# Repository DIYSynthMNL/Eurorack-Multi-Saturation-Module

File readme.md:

# Synth Distortion / Saturation Module Design

## Revision Summary

- Schematic Revision 0.5 - an easier to read schematic - please note that there are some errors in this. The Eurorack power connector pins are backwards. Use this as a reference for the circuit design.
- Schematic Revision 0.6 - multiboard layout (LATEST - working on circuit revisions)
- PCB Revision 0.1 - revising in progress (working on rev 0.2)

## Some background.

I’m designing a distortion/saturation modular synth module using different methods of distorting audio signals.

This module is a combination of transformer, opto, and clipping distortion/saturation.

## Source of inspiration

Local archived copies of the borrowed-source schematics live in [`references/`](references/) so this repo stays useful if the upstream links die. Originals from [diyrecordingequipment.com](https://www.diyrecordingequipment.com/pages/the-colour-format).

- **CTX Cinemag Transformer Colour mkII** — [local copy](references/DIYRE-CTX-Cinemag-mkII-schematic.pdf) · [upstream](https://cdn.shopify.com/s/files/1/0698/2265/files/CTX_mkII_Schematic.pdf?375)
- **Colourphone (v1.3)** — [local copy](references/DIYRE-Colourphone-schematic-v1.3.pdf) · [upstream](https://cdn.shopify.com/s/files/1/0698/2265/files/XQP_Colourphone_Schematic_1.3.pdf?8973696934571457842)
- **Colourupter (v1.7)** — [local copy](references/DIYRE-Colourupter-schematic-v1.7.pdf) · [upstream](https://cdn.shopify.com/s/files/1/0698/2265/files/XQP_Colourupter_Schematic_1.7.pdf?13355729951948932441)

### DIYRe’s Colour Modules

I got some ideas from DIYRe's Colour modules. DIYRe is a company that produces DIY kits for professional audio recording equipment. Some of their product offerings include recording studio rackmount effects.

[The Colour Format](https://www.diyrecordingequipment.com/pages/the-colour-format)

| Colour Module | What does it do? | What ideas did you get? | Link to page | Schematic |
| --- | --- | --- | --- | --- |
| CTX Transformer Colour | A transformer saturation module with a discrete opamp and a Cinemag audio transformer which has a 1:1 turns ratio. | Non-inverting amp to drive the transformer past what it can handle. Resistor before the transformer that isolates the opamp from the transformer. | https://www.diyrecordingequipment.com/products/ctx-cinemag-transformer-colour-mkii | https://cdn.shopify.com/s/files/1/0698/2265/files/CTX_mkII_Schematic.pdf?375 |
| Colourphone | A telephone sound emulator. It uses a bandpass filter and a 1:1 turn ratio audio transformer. | I have a similar transformer which is a 600:600 ohm transformer. Resistor before the transformer that isolates it from the opamp. | https://www.diyrecordingequipment.com/products/colourphone-telephone-distortion-colour | https://cdn.shopify.com/s/files/1/0698/2265/files/XQP_Colourphone_Schematic_1.3.pdf?8973696934571457842 |
| Colourupter | An opto distortion module that is vactrol based. | Using a vactrol and the circuit around it. IC1c and IC1d only. | https://www.diyrecordingequipment.com/products/colourupter | https://cdn.shopify.com/s/files/1/0698/2265/files/XQP_Colourupter_Schematic_1.7.pdf?13355729951948932441 |

### Other sources

- Vactrol wet/dry mix from music thing modular’s spring reverb module
    - [https://www.musicthing.co.uk/Spring-Reverb/](https://www.musicthing.co.uk/Spring-Reverb/)
- Eliot Sound Products [https://sound-au.com](https://sound-au.com/) - is a website full of audio articles that I’ve learned from. Go search for these articles, they’re great!
    - Designing With Op Amps
    - Audio Transformers
    - Soft Clipping

# Circuit Design

- I will update this section soon.

### Stages

1. Input gain stage (buffer only, see design note below)

    We must take into account the headroom of the op amp. The NE5532 can only output 2 volts less than the supply voltage. So for example, your supply voltage would be +/- 12V, your max output would be 10V based on the image below.

    A buffer would suffice as the input stage. It would be nice to give the transformer more voltage but we wouldn’t be able to amplify the 10Vpp input to 12Vpp unless we use a +/- 15V supply. 
    
    I chose to use an NE5532 Op Amp because I believe it can drive outputs higher than TL07x.
    
2. Transformer Saturation
    
    The transformer distortion works by oversaturating the transformer’s core past what it can handle. The transformer I used would normally be used in line audio signals. A 600:600 ohm transformer. We’re using Eurorack voltage which is around 10vpp so that would oversaturate the transformer.

3. Vactrol Opto Electronic Saturation
    
    The transformer’s output was low, I needed to add a non-inverting op amp with gain to bring the levels back to 10vpp for this stage.
    
    I got this circuit from DIYRe’s Colourupter colour module which uses a Vactrol to clip the signal.

4. Soft Clipping Diode Saturation
    
    I chose to place these diodes after the wet amplifier. It would be softer if I placed it before the U4A. I chained LEDs to the 1N4148s to get a softer clipping effect. LEDs alone would make saw waves looking like square waves.

5. Voltage controlled Vactrol Wet/Dry mix
    
    I used my handmade Vactrol. I made it using a 5mm diffused red LED and a 5mm LDR enclosed with black heat shrink tubing. I crimped the ends so no light would leak in. 47k works for R17 with my Vactrol.

## Schematic Revisions:

- Revision 0.2
    - TODO
        - [x]  Replace R5 with trimmer
        - [x]  Test wet/dry mix on breadboard
        - [x]  Input buffer biasing resistor
    - Notes
        - The transformer saturation is very subtle on a mono synth
- Revision 0.3
    - TODO
    - [x]  Add gain trimmer to dry signal at U2B
    - [x]  Scrap the single saturation and add diode clipping and the Colourupter, the transformer alone is too subtle
    - [x]  Test output gain stage
- Revision 0.4
    - [x]  Scrap output auto gain
    - [x]  add opto saturation
    - [x]  add soft clipping diodes
- Revision 0.5
    - [x]  Multiboard layout
- Revision 0.6
    - [ ]  Fix amplitude difference on opto sat stage output.

# PCB Design

Dec 27, 2023 - Almost satisfied  with the board design, rev0.1

Rev 0.1 in black

## PCB revisions:

- Todo for Revision 0.1
    - [x]  Ground plane vias
    - [x]  Front panel ground plane
    - [x]  Double check hole sizes
        - [x]  Trimmer
    - [x]  Double check via sizes
    - [x]  Round tracks
- Todo for Revision 0.2
    - Front panel
        - [x]  Add keep out zone for led window zone fills for FCU and BCU - I had to Dremel it out for the revision 0.1 front panel board
        - [x]  Enlarge switch holes for Dailywell switches
        - [x]  Enlarge trimmer holes
        - [x]  Change tilt knob silkscreen to “mix”
        - [ ]  Fix amplitude difference on opto sat output. The opto stage attenuates the signal from the transformer too much
- Revision 0.1 Board test notes
    - Voltage tests
        - Power rails after reverse protection diode I used a 1N4007 diode
            - V+ reads about 10V
            - V- reads about 11V
            - I might need to change the reverse protection diodes to Schottkys
    - Music thing modular’s cv wet dry circuit has an optimal input of 0-5V control voltages. If 10Vpp was used, the middle of the cv level pot is zero. Fully clockwise, the cv would be in phase. Fully counter clockwise, the cv is inverted. This is simulated in falstad, the file is included in the falstad folder.
    - Gain trim is finicky. Turning on the Opto would attenuate the signal. Maybe this is caused by the variety of the vactrol, I think not all vactrols are equal. Opto gain/amplitude trim might be required. It might be a simple resistor value change within the circuit.
    - LEDs are not as bright as I want them.

## Circuit walkthrough

Three saturation stages in series, each individually bypassable from the front panel, then a CV-controlled wet/dry mix:

```
Audio In ─► U1A buffer ─┬─► [Dry path → wet/dry mixer U4B]
                        │
                        └─► SW1 (Xformer bypass) ─► [TL016 transformer, 680Ω matching, HPF 15Hz]
                                                  ─► U1B buffer ─► transformer-saturated signal
                                                                     │
                                                                     ▼
                                                  SW2 (Opto bypass) ─► U2A buffer ─► C2 (1µF) ─► U2B inverting amp (gain −68)
                                                                                                    ├─► drives U3 vactrol LED (R10 limits)
                                                                                                    └─► AC-coupled out as "Wet"
                                                                                                                                ▼
                                              U4A amp ────────► clipping LEDs + 1N4148 (SW1 on Board B bypasses)
   Dry signal ──► U4B amp ───────────────────┘                                                              │
                                                                                                            ▼
                                                                                  U6 vactrol (CV wet/dry mixer, driven by Mix CV via U5A/U5B)
                                                                                                            ▼
                                                                                                       Mix Audio Out
```

### Three saturation flavors, switchable

**1. Transformer saturation (TL016-R, 600:600Ω).** 680Ω resistors match the transformer's characteristic impedance. Driving the primary hard pushes the magnetic core into non-linearity — classic warm "tape-like" harmonic content (mostly odd harmonics). The 15Hz HPF (C1 + R7) on the secondary removes any DC bias.

**2. Opto-electronic saturation (vactrol, U3).** U2B is a high-gain inverting amp (R8/R6 = 680/10 = **−68× gain**) driving the vactrol's LED. As the signal gets louder, the LED brightens, the LDR resistance drops, more signal shunts to ground — soft compression / saturation. Fast attack/release due to the vactrol's photo response.

**3. Diode soft clipping (Board B).** LEDs (D1, D2) in series with 1N4148s (D3, D4) — asymmetric soft clipping with the LEDs adding ~2V of softness before the 4148s contribute hard clip. Pleasant warmth without harsh square-wave look. SW1 on Board B bypasses.

### Wet/Dry mix (CV-controlled)

Borrowed from Music Thing Modular's Spring reverb topology. Second vactrol (U6) acts as a CV-controlled variable resistor in the mix path. Mix CV input → U5A → U5B → vactrol LED. The Mix Trim pot (RV4, 50K) shifts the CV center point by ±12V so the vactrol's response curve aligns with your CV source (the Music Thing original optimizes for 0–5V CV; this tuning lets it handle ±5V or other ranges).

### Calibration

Three trim pots accessible from the front panel:

**RV2 — Wet gain trim.** Sets U4A's amplification of the wet (saturated) signal. Goal: match the wet signal's amplitude to the dry signal so the mix knob crossfades cleanly.

**RV3 — Dry gain trim.** Sets U4B's amplification of the dry signal. Adjust together with RV2 until at the mix midpoint, the output amplitude doesn't jump as you switch saturation stages on/off.

**RV4 — Mix trim.** Shifts the Mix CV bias up or down ±12V. Adjust until the panel mix pot's full clockwise position gives 100% wet and full counter-clockwise gives 100% dry, with your CV source connected. With no CV connected (or 0V), midpoint should give 50/50.

Procedure:
1. Patch a steady audio signal (e.g., a sawtooth from a VCO) into Audio In.
2. Set all bypass switches to "off" (no saturation) — only the dry path is active.
3. Patch a scope on Mix Audio Out. Note the amplitude.
4. Switch in transformer saturation (SW1). Adjust RV2 (wet gain) so the amplitude is similar to dry.
5. Switch in opto saturation (SW2). If the amplitude drops dramatically here, see [issue #1](https://github.com/DIYSynthMNL/Eurorack-Multi-Saturation-Module/issues) for the known opto-sat fix.
6. With a 0–5V LFO into Mix CV, adjust RV4 (mix trim) so panel mix pot fully clockwise = wet, fully counter-clockwise = dry.

## Build status

What's ready for builders today, and what's still on the TODO list:

**Production assets** (what you need to actually fabricate and assemble a final unit)

- [x] Schematic — Rev 0.6 ([Single saturation module - Multiboard Schematic - rev0.6.pdf](Schematic%20PDFs/Single%20saturation%20module%20-%20Multiboard%20Schematic%20-%20rev0.6.pdf))
- [x] PCB layout — rev 0.1 separated for fab in `kicad/Separate boards/rev 0.1/`; rev 0.2 fixes pending (see PCB revisions in readme)
- [ ] Gerber files for fabrication — none yet
- [x] BOM — [ibom.html](BOMs/ibom.html)
- [x] Final front panel (SVG/PDF for fab) — [MultiSaturation_FPANEL_FOR_KICAD_IMPORT.svg](Front%20panel%20graphics/MultiSaturation_FPANEL_FOR_KICAD_IMPORT.svg)
- [x] License — [LICENSE](LICENSE)

**Prototype assets** (for breadboard / perfboard / 3D-printed-panel builds before final PCB)

- [ ] 3D-printed prototype panel STL — none yet

**Documentation**

- [x] Photos of the assembled module — see [photos/](photos/)
- [ ] Demo video — none yet
- [ ] Build / assembly instructions — none yet
- [ ] Calibration / tuning notes — none yet

Want to help fill a gap (build photos, gerbers, an assembly guide)? Open an issue or PR.

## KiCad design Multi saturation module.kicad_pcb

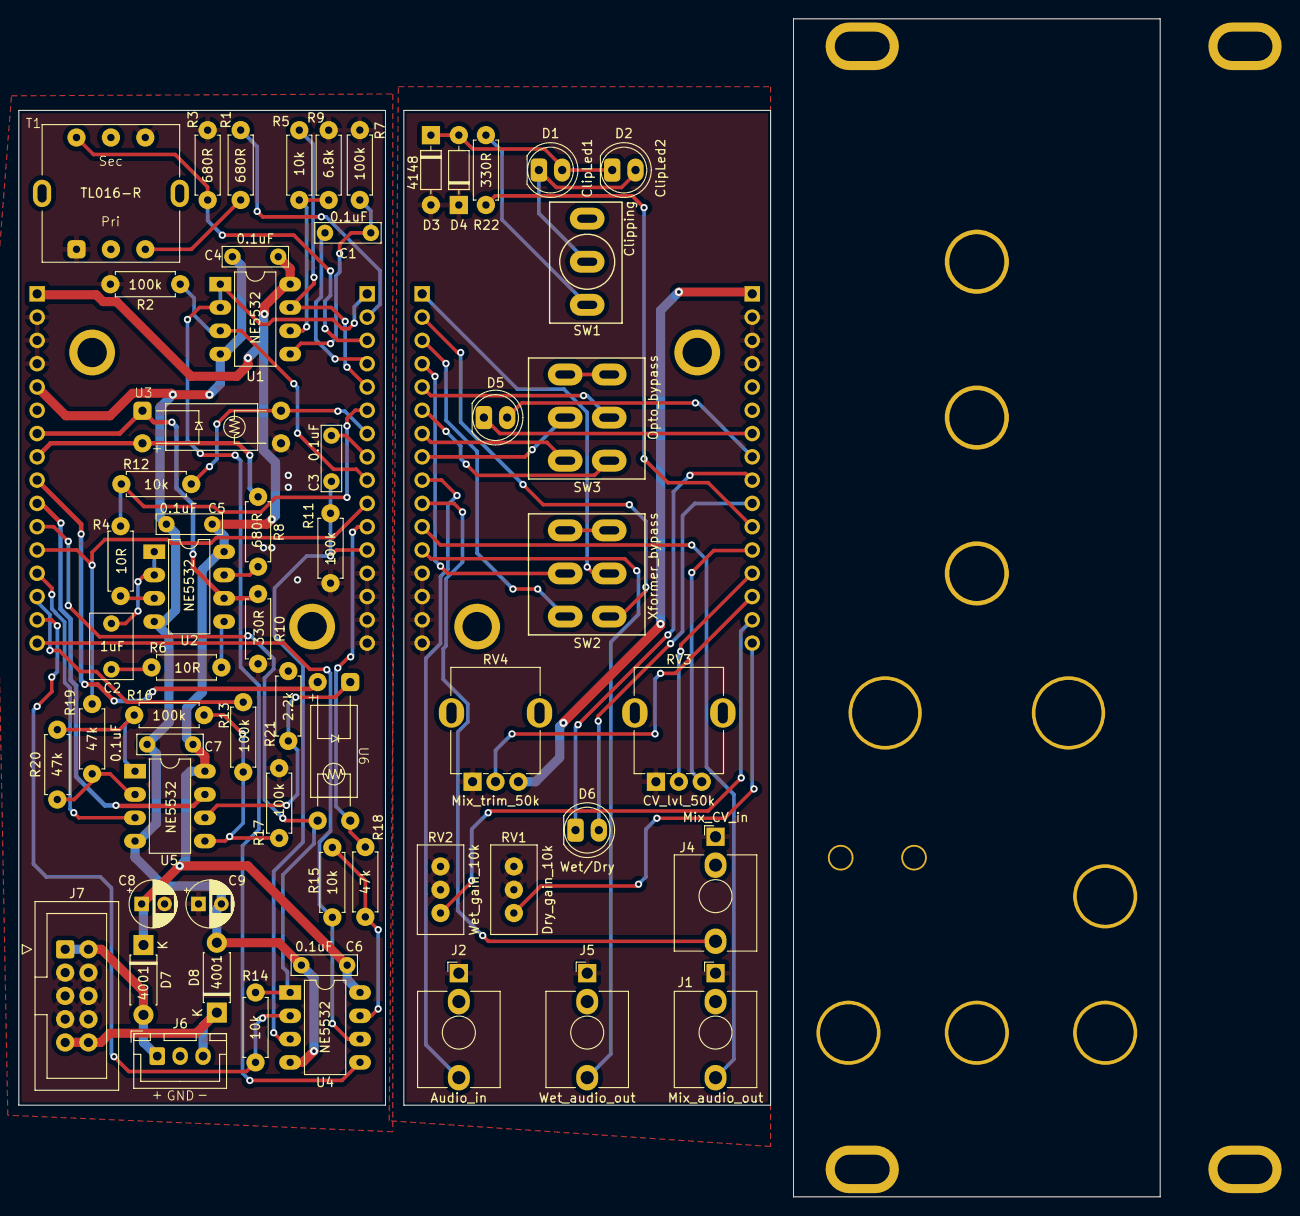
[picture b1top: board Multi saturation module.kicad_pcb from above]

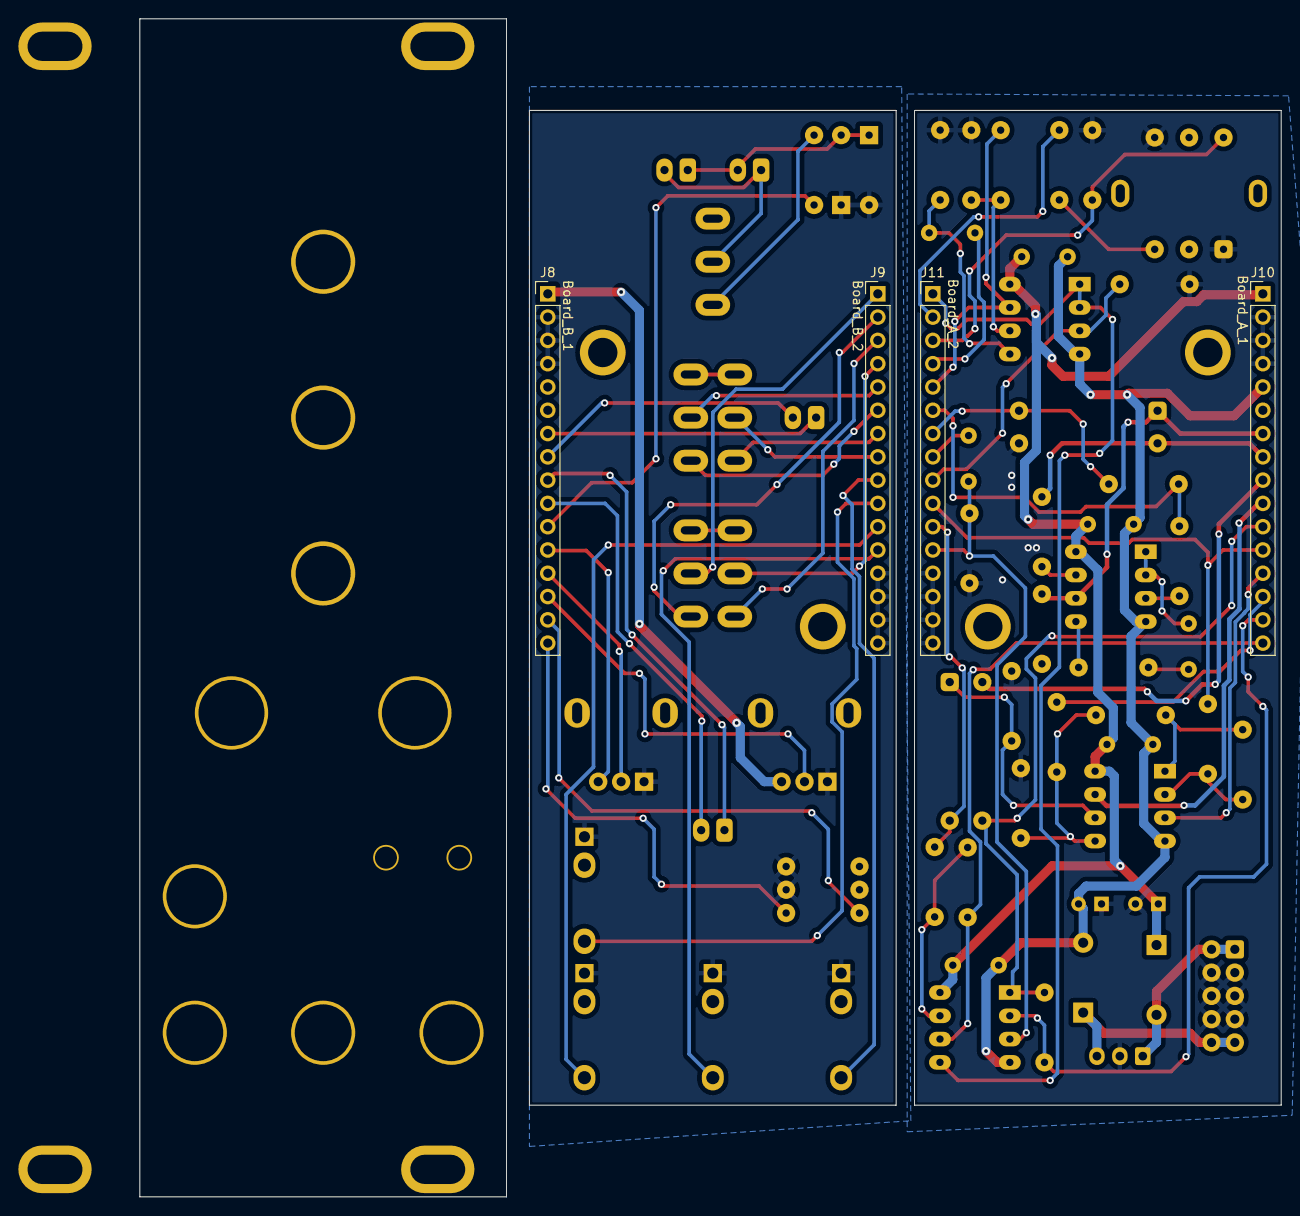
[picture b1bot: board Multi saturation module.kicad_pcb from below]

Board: 2 copper layers, 124.5 x 128.5 mm, 63 parts (4 on the bottom side), 68 nets.

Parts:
C1, C3, C4, C5, C6, C7: 0.1uF; C_Rect_L7.0mm_W2.0mm_P5.00mm_BigPads
C2: 1uF; C_Rect_L7.0mm_W4.5mm_P5.00mm_BigPads
C8, C9: 22uF; CP_Radial_D5.0mm_P2.50mm
D1: ClipLed1; LED_D5.0mm_BigPads
D2: ClipLed2; LED_D5.0mm_BigPads
D3, D4: 4148; D_4148_BigPads
D5: Opto_sat; LED_D5.0mm_BigPads
D6: Wet/Dry; LED_D5.0mm_BigPads
D7, D8: 4001; D_DO-41_SOD81_P7.62mm_Horizontal_BigPads
J1: Mix_audio_out; AudioJack_3.5mm_long_pads
J2: Audio_in; AudioJack_3.5mm_long_pads
J4: Mix_CV_in; AudioJack_3.5mm_long_pads
J5: Wet_audio_out; AudioJack_3.5mm_long_pads
J6: EuroPower_JST_3P; Eurorack_power_jst_3P
J7: EURO_PWR_2x5; IDC-Header_2x05_P2.54mm_Vertical_BigPads
J8: Board_B_1; PinHeader_1x16_P2.54mm_Vertical
J9: Board_B_2; PinHeader_1x16_P2.54mm_Vertical
J10: Board_A_1; PinHeader_1x16_P2.54mm_Vertical
J11: Board_A_2; PinHeader_1x16_P2.54mm_Vertical
R1, R3, R8: 680R; R_quarter_watt_L6.3mm_D2.5mm_P7.62mm
R2, R7, R11, R13, R16, R17: 100k; R_quarter_watt_L6.3mm_D2.5mm_P7.62mm
R4, R6: 10R; R_quarter_watt_L6.3mm_D2.5mm_P7.62mm
R5, R12, R14, R15: 10k; R_quarter_watt_L6.3mm_D2.5mm_P7.62mm
R9: 6.8k; R_quarter_watt_L6.3mm_D2.5mm_P7.62mm
R10, R22: 330R; R_quarter_watt_L6.3mm_D2.5mm_P7.62mm
R18, R19, R20: 47k; R_quarter_watt_L6.3mm_D2.5mm_P7.62mm
R21: 2.2k; R_quarter_watt_L6.3mm_D2.5mm_P7.62mm
RV1: Dry_gain_10k; Potentiometer_Bourns_3296W_Vertical_BigPads
RV2: Wet_gain_10k; Potentiometer_Bourns_3296W_Vertical_BigPads
RV3: CV_lvl_50k; Potentiometer_RV09_BigPads
RV4: Mix_trim_50k; Potentiometer_RV09_BigPads
SW1: Clipping; ToggleSwitch_MTS-102_SPDT
SW2: Xformer_bypass; ToggleSwitch_MTS-202_DPDT
SW3: Opto_bypass; ToggleSwitch_MTS-202_DPDT
T1: TL016-R; Audio_transformer_TL016-R
U1, U2, U4, U5: NE5532; DIP-8_W7.62mm_LongPads
U3, U6: VTL5C; Handmade_vactrol_5mm

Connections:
+12V: C4.1, C5.1, C6.1, C7.1, C8.1, D7.1 (K), J10.1, U1.8 (V+), U2.8 (V+), U4.8 (V+), U5.8 (V+)
+12VA: J8.1, RV4.3
-12V: C4.2, C5.2, C6.2, C7.2, C9.2, D8.2 (A), J10.5, U1.4 (V-), U2.4 (V-), U4.4 (V-), U5.4 (V-)
/Board_A/+12V_IN: D7.2 (A), J6.1 (+12v), J7.1 (+12V), J7.2 (+12V)
/Board_A/-12V_IN: D8.1 (K), J6.3 (-12v), J7.9 (-12V), J7.10 (-12V)
Audio_in: J11.9, R2.1, U1.3 (+)
Audio_in_B: J2.T, J9.9
Clipping_diodes: J10.11, R14.1, U4.1, U6.4
Clipping_diodes_B: J8.11, R22.2
D1_+: J10.8, R8.1, U3.2 (+)
D1_+_B: D5.2 (A), J8.8
D1_-: J10.7, R10.1, U2.6 (-), U3.1 (-)
D1_-_B: D5.1 (K), J8.7
D4_+: J10.10, U5.7
D4_+_B: D6.2 (A), J8.10
D4_-: J10.9, U6.2 (+)
D4_-_B: D6.1 (K), J8.9
Dry: J11.1, U1.1, U1.2 (-), U4.5 (+)
GND: C8.2, C9.1, J6.2 (GND), J7.3 (GND), J7.4 (GND), J7.5 (GND), J7.6 (GND), J7.7 (GND), J7.8 (GND), J10.2, J10.3, J10.4, J11.13, J11.14, J11.15, J11.16, R2.2, R3.1, R7.2, R9.2, R10.2, R11.2, R17.2, R21.2, T1.1, T1.4, U3.4
GND1: D3.2 (A), D4.1 (K), J1.S, J2.S, J4.S, J5.S, J8.2, J8.3, J8.4, J9.13, J9.14, J9.15, J9.16, RV1.1, RV1.2, RV2.1, RV2.2, RV3.1, RV4.1
Mix_CV_in: J10.12, J11.10, R19.1
Mix_CV_in_B: J4.T, J9.10
Mix_audio_out: J11.11, R18.1, U6.3
Mix_audio_out_B: J1.T, J9.11
unnamed: C2.2, R6.1
unnamed: D1.2 (A), D2.1 (K), D3.1 (K), D4.2 (A)
unnamed: D1.1 (K), D2.2 (A), SW1.2 (B)
unnamed: R1.2, T1.3
unnamed: R8.2, U2.7
unnamed: R15.1, R18.2, U4.7
unnamed: R16.2, R20.2, U5.1
unnamed: R22.1, SW1.1 (A)
unnamed: SW2.3 (C), SW2.6 (C)
unnamed: SW3.3 (C), SW3.6 (C)
unnamed: C1.1, R7.1, U1.5 (+)
unnamed: R5.1, R9.1, U1.6 (-)
unnamed: R4.2, U2.3 (+)
unnamed: C2.1, U2.1, U2.2 (-)
unnamed: R6.2, U2.5 (+)
unnamed: R19.2, R20.1, U5.2 (-)
unnamed: R13.2, R16.1, R17.1, U5.5 (+)
unnamed: R21.1, U5.6 (-), U6.1 (-)
RV1_2: J10.14, R13.1
RV1_2_B: J8.14, RV4.2
RV2_3: J10.15, R14.2, U4.2 (-)
RV2_3_B: J8.15, RV2.3
RV3_3: J10.16, R15.2, U4.6 (-)
RV3_3_B: J8.16, RV1.3
RV4_2: J10.13, U5.3 (+)
RV4_2_B: J8.13, RV3.2
RV4_3_B: J8.12, RV3.3
SW1_1: J11.2, R1.1
SW1_1_B: J9.2, SW2.1 (A)
SW1_2_B: J9.1, SW2.2 (B)
SW1_4: J11.3, R3.2, T1.6
SW1_4_B: J9.3, SW2.4 (A)
SW1_5: C1.2, J11.4
SW1_5_B: J9.4, SW2.5 (B)
SW2_1: J11.6, R4.1, R12.2
SW2_1_B: J9.6, SW3.1 (A)
SW2_2: J11.5, R5.2, U1.7
SW2_2_B: J9.5, SW3.2 (B)
SW2_4: J11.7, R12.1, U3.3
SW2_4_B: J9.7, SW3.4 (A)
SW2_5: C3.2, J11.8
SW2_5_B: J9.8, SW3.5 (B)
Wet: C3.1, J11.12, R11.1, U4.3 (+)
Wet_B: J5.T, J9.12

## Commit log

2023-12-19 Create LICENSE
2023-12-20 version 0.3 update
2023-12-21 version 0.3 readme update
2023-12-21 renamed the project
2023-12-22 revision 0.4
2023-12-23 revision 0.4 update
2023-12-24 rev 0.5 update
2023-12-24 Revision 5 update
    This commit is before I separate the schematic parts into boards.
2023-12-24 Separate boards branch started
2023-12-25 Laid out footprints on three boards
2023-12-25 board update
2023-12-25 All boards routed
2023-12-25 board routing update
2023-12-25 routing with bigger traces finished
2023-12-25 board connector wrong placement fix
2023-12-27 Front panel graphics updated
2023-12-28 added rev 0.5 and 0.6 schematic pdfs
2023-12-28 cleaned up project directory
2023-12-28 Added pcb sheet details
2023-12-29 board and schematic update
2023-12-30 Kikit Multiboard to single board excecuted for all boards
2024-01-02 Rounded tracks update
2024-01-05 multiboard update, rounded tracks
2024-01-06 gerbers updated
2024-01-09 ibom and schematic update
2024-01-14 revision 0.2 started
2024-01-22 added kicad gitignore
2026-05-14 Clean up repo cruft
2026-05-14 Add Build status checklist to README
2026-05-14 Fix Build status link path case
2026-05-14 Rewrite Build status with per-module accuracy
2026-05-14 Add photos/ placeholder for assembled-module shots
2026-05-14 Add assembled-module photos and update README hero
2026-05-14 Add JPGs converted from raws and clean photo dirs
2026-05-14 Rename photos to descriptive names; pick hero images
2026-05-14 Add circuit walkthrough and calibration procedure to README
2026-05-14 Add references/ folder with archived DIYRe Colour schematics
    Local copies of the three borrowed sources cited in the README: CTX
    Cinemag mkII, Colourphone v1.3, and Colourupter v1.7. Originals are
    on diyrecordingequipment.com's CDN, which could go away.
